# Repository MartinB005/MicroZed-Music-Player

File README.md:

# DIY Music Player using MicroZed

This is low-level music player written in C/C++ with custom DA Converter as an audio output. It includes simple GUI with file browser and playing controls, 
which is rendering on 320 x 480 LCD. It is controlled by rotary encoders. Current audio level is shown by 32-LED line. See full documentation [here](https://martinb005.github.io/MicroZed-Music-Player).

## Target Device
- MICROZED EVALUATION KIT ADSAES-Z7MB-7Z010-G
- CPU: Dual ARM® Cortex™-A9 MPCore™ @ 866 MHz (NEON™ & Single / Double Precision Floating Point)
- Operating system: GNU/Linux
- Development kit MicroZed APO (https://gitlab.com/pikron/projects/mz_apo/microzed_apo)

## Supported Audio Formats
- 16-bit PCM WAV, stereo (2-channel), uncompressed
- MPEG-1 Layer III (MP3), stereo, lossy compression

## DA Converter
- 10-bit R2R digital to analog converter with LM386 amplifier
- 2x 74HC595 shift register
- Jack 3.5 mm and terminal block for speaker
- See [dac.sch](dac-design/dac.sch) and [dac.brd](dac-design/dac.brd)

Current implementation uses 3 GPIO pins and 2 shift registers (see [DAC.cpp](peripherals/DAC.cpp) and [mzapo_regs.h](core/mzapo_regs.h) where are adresses of mapped pins).
It is possible to do it without shift registers, if you have 10 free GPIO-s.

## Instalation
```bash
# clone the repo
git clone https://github.com/MartinB005/MicroZed-Music-Player.git

# Navigate to the directory
cd MicroZed-Music-Player

# Edit your local IP address in Makefile
TARGET_IP ?= xxx.xxx.xxx.xxx

# compile and run the program
make run
```

## Used Libraries
MP3 decoding:
https://github.com/lieff/minimp3

## Demonstration Videos
https://github.com/user-attachments/assets/9bd06672-fdcf-4da8-a37d-1d057ed24d74

https://github.com/user-attachments/assets/56f21344-d6c7-4b53-9a67-5a15862af7fc

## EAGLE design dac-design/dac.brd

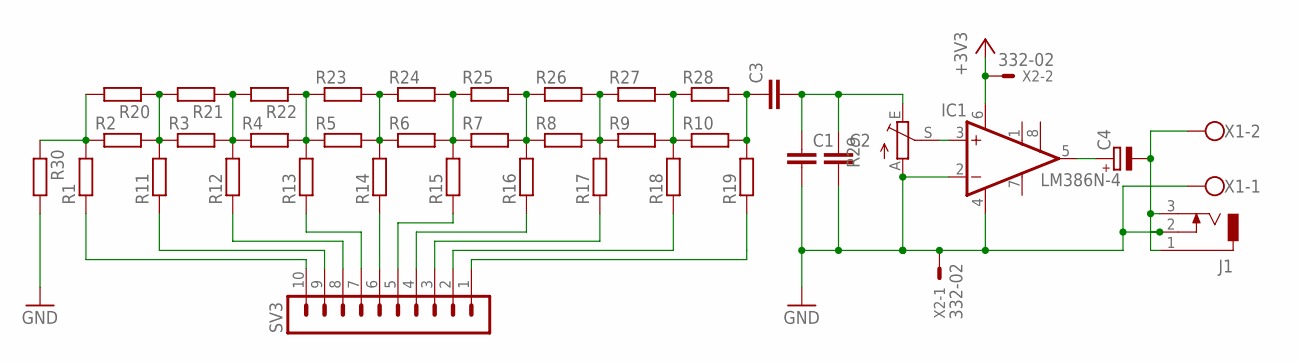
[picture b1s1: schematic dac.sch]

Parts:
C1, C2, C3: C5/4.5; C5B4.5
C4: CPOL-EUE5-6; E5-6
IC1: LM386N-4; DIL08
J1: DCJ0303
R1, R2, R3, R4, R5, R6, R7, R8, R9, R10, R11, R12, R13, R14, R15, R16, R17, R18, R19, R20, R21, R22, R23, R24, R25, R26, R27, R28, R30: R-EU_0309/10; 0309/10
R29: TRIM_EU-CA9V; CA9V
SV3: MA10-1W
X1: W237-102
X2: 332-02

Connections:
+3V3: IC1.6 (VS), X2.2
GND: C1.2, C2.2, IC1.2 (-IN), IC1.4 (GND), J1.2, R29.A, R30.2, X1.1, X2.1
unnamed: IC1.3 (+IN), R29.S
unnamed: R2.2, R3.1, R11.2, R20.1, R21.2
unnamed: R3.2, R4.1, R12.2, R21.1, R22.2
unnamed: R4.2, R5.1, R13.2, R22.1, R23.1
unnamed: R5.2, R6.1, R14.2, R23.2, R24.1
unnamed: R6.2, R7.1, R15.2, R24.2, R25.1
unnamed: R7.2, R8.1, R16.2, R25.2, R26.1
unnamed: R8.2, R9.1, R17.2, R26.2, R27.1
unnamed: R9.2, R10.1, R18.2, R27.2, R28.1
unnamed: C1.1, C2.1, C3.2, R29.E
unnamed: R19.1, SV3.1
unnamed: R18.1, SV3.2
unnamed: R17.1, SV3.3
unnamed: R16.1, SV3.4
unnamed: R15.1, SV3.5
unnamed: R14.1, SV3.6
unnamed: R13.1, SV3.7
unnamed: R12.1, SV3.8
unnamed: R11.1, SV3.9
unnamed: R1.1, SV3.10
unnamed: C3.1, R10.2, R19.2, R28.2
unnamed: C4.-, J1.1, J1.3, X1.2
unnamed: C4.+, IC1.5 (OUT)
unnamed: R1.2, R2.1, R20.2, R30.1

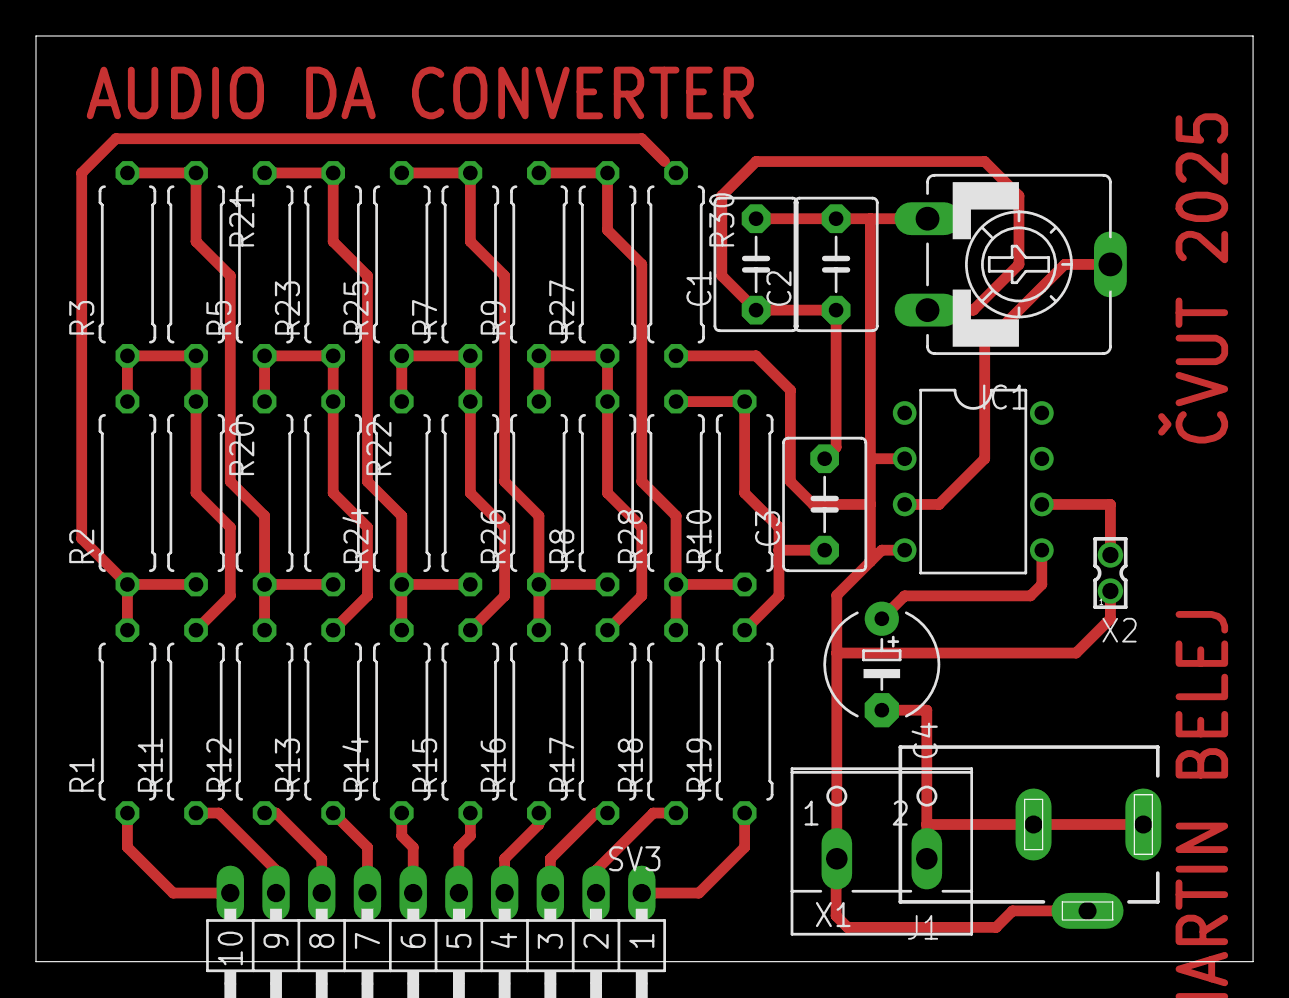
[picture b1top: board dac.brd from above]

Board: 2 copper layers, 67.6 x 51.4 mm, 39 parts (0 on the bottom side), 26 nets.

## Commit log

2025-05-09 first-commit
2025-05-11 new project structure
2025-05-11 gitignore
2025-05-11 mp3 supportt
2025-05-15 playingView + volumeView
2025-05-17 Add README.md
2025-05-18 add dac-design folder
2025-05-19 add docs
2025-05-19 github actions
2025-05-19 deploy: 9fefe820840d087d81ed1dc3839f6151cfc6cfba
2025-05-19 edit docs
2025-05-19 deploy: c6274028e4638ba5c7851ecc1e2ea7184acd4721
2025-05-19 deploy: 3a0e3174edaddbb8a25b0c27f5f8f1f531262cff
2025-05-19 deploy: 245b21c593678e220f31e3e20916d6ca32c1febd
2025-05-19 deploy: 2a650b0def15f2de02d024391323443a2c35e688
2025-05-19 deploy: 9b905bb01f4158ec3d28d723117bad0ea6da2bf6
2025-05-19 deploy: f0ea7ddde7ace4068adc8cf36dc32909836bef27
2025-05-19 deploy: 8a2188d2fb5c5a05ed409d8b4ff314be626e3fe2
2025-05-19 deploy: e892e341a54616005941d0c8389ed93de8bc5c6e
2025-05-19 deploy: 84cea78fd2df45acaa7564801123225daba2737d
2025-05-19 deploy: 55827b7913daad1b8afe2c0bc959d39e5b651573
